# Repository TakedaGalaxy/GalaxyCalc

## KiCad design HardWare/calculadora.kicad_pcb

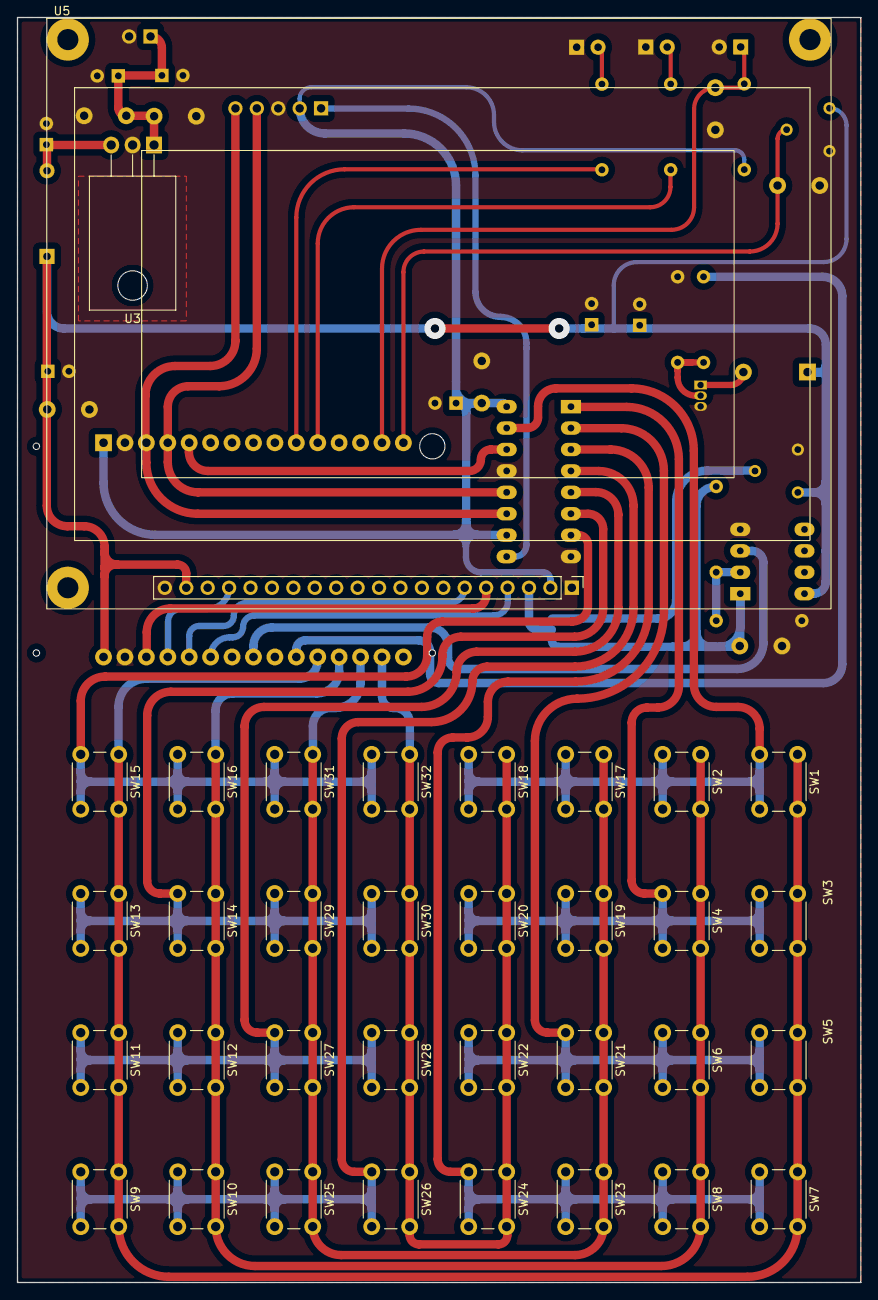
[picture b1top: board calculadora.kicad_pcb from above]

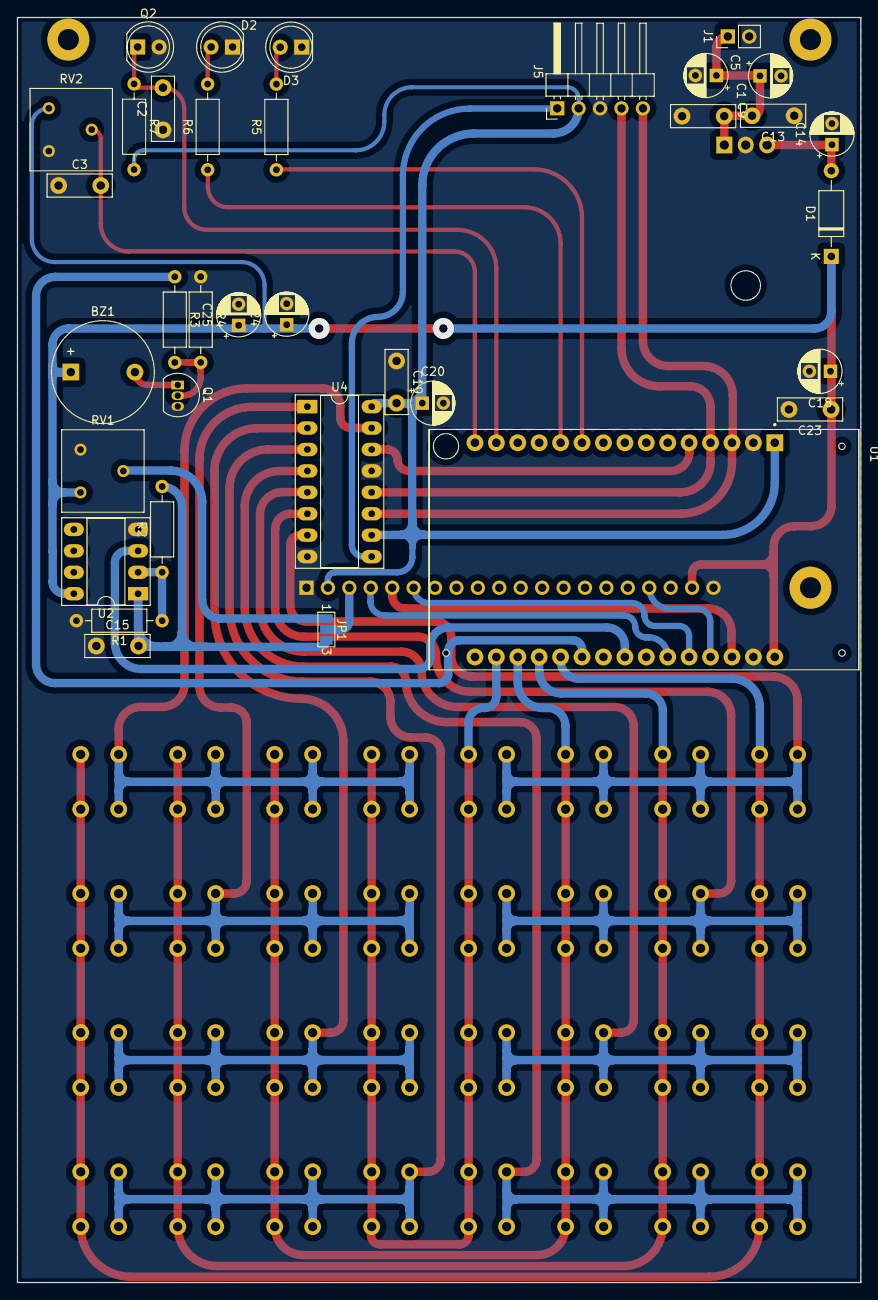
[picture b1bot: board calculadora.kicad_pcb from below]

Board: 2 copper layers, 100.0 x 150.0 mm, 69 parts (35 on the bottom side), 39 nets.

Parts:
BZ1: Buzzer; Buzzer_12x9.5RM7.6
C1, C24: 100UF/50v; CP_Radial_D5.0mm_P2.50mm
C2, C3, C9, C13, C15, C19: 0.1uf; C_Disc_D7.5mm_W2.5mm_P5.00mm
C5, C14, C18, C20, C25: 10UF/35V; CP_Radial_D5.0mm_P2.50mm
C23: 0.1uF; C_Disc_D7.5mm_W2.5mm_P5.00mm
D1: D_Schottky; D_A-405_P10.16mm_Horizontal
D2: LED_RED; LED_D5.0mm
D3: LED_IR; LED_D5.0mm
J1: Screw_Terminal_01x02; PinHeader_1x02_P2.54mm_Vertical
J5: Conector ShiftRegister; PinHeader_1x05_P2.54mm_Horizontal
JP1: Jumper_3_Open; SolderJumper-3_P1.3mm_Open_Pad1.0x1.5mm_NumberLabels
Q1: Q_NPN_CBE; TO-92L_Inline
Q2: Q_Photo_NPN; LED_D5.0mm
R1: 20K; R_Axial_DIN0207_L6.3mm_D2.5mm_P10.16mm_Horizontal
R2: 11K; R_Axial_DIN0207_L6.3mm_D2.5mm_P10.16mm_Horizontal
R3: 1K; R_Axial_DIN0207_L6.3mm_D2.5mm_P10.16mm_Horizontal
R4: 10K; R_Axial_DIN0207_L6.3mm_D2.5mm_P10.16mm_Horizontal
R5, R6: 100; R_Axial_DIN0207_L6.3mm_D2.5mm_P10.16mm_Horizontal
R7: 100K; R_Axial_DIN0207_L6.3mm_D2.5mm_P10.16mm_Horizontal
RV1, RV2: 10K; Potentiometer_Bourns_3386F_Vertical
SW1, SW2, SW3, SW4, SW5, SW6, SW7, SW8, SW9, SW10, SW11, SW12, SW13, SW14, SW15, SW16, SW17, SW18, SW19, SW20, SW21, SW22, SW23, SW24, SW25, SW26, SW27, SW28, SW29, SW30, SW31, SW32: chave_tactil; SW_PUSH_6mm_H5mm
U1: ESP32-DEVKIT-V1; MODULE_ESP32_DEVKIT_V1
U2: LM358; DIP-8_W7.62mm_Socket_LongPads
U3: LM7805_TO220; TO-220-3_Horizontal_TabDown
U4: M74HC595B1; DIP-16_W7.62mm_Socket_LongPads
U5: LCD_GRAFICO_ST920; Display 128x64

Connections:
+3V3: C19.2, C20.1, J5.2, R7.2, U1.1 (3V3), U4.10 (!SCLR), U4.16 (VCC), U5.2 (Vdd)
+5V: BZ1.1 (-), C18.1, C23.1, C24.1, C25.1, D1.1 (K), RV1.1, RV2.3, U1.30 (VIN), U2.8 (V+), U5.19 (A(+))
Buzzer: R3.1, U1.21 (D32)
C1: SW1.2, SW2.2, SW17.2, SW18.2, U4.15 (QA)
C2: SW3.2, SW4.2, SW19.2, SW20.2, U4.1 (QB)
C3: SW5.2, SW6.2, SW21.2, SW22.2, U4.2 (QC)
C4: SW7.2, SW8.2, SW23.2, SW24.2, U4.3 (QD)
C5: SW9.2, SW10.2, SW25.2, SW26.2, U4.4 (QE)
C6: SW11.2, SW12.2, SW27.2, SW28.2, U4.5 (QF)
C7: SW13.2, SW14.2, SW29.2, SW30.2, U4.6 (QG)
C8: SW15.2, SW16.2, SW31.2, SW32.2, U4.7 (QH)
CLOCK_SHIFT: J5.5, U1.3 (D15), U4.11 (SCK)
DAC1: U1.23 (D25), U2.3 (+)
DADO_SHIFT: U1.5 (D4), U4.14 (SI)
Enable: U1.26 (D14), U5.6 (E)
GND: C1.2, C2.1, C3.1, C5.2, C9.1, C13.1, C14.2, C15.1, C18.2, C19.1, C20.2, C23.2, C24.2, C25.2, D2.1 (K), D3.1 (K), J1.2, J5.3, Q1.3 (E), Q2.2 (E), R1.2, R4.1, RV1.3, RV2.1, U1.2 (GND), U1.29 (GND), U2.4 (V-), U3.2 (GND), U4.8 (GND), U4.13 (!G), U5.1 (Vss), U5.20 (K(-))
L1: SW1.1, SW3.1, SW5.1, SW7.1, SW9.1, SW11.1, SW13.1, SW15.1, U1.20 (D35)
L2: SW2.1, SW4.1, SW6.1, SW8.1, SW10.1, SW12.1, SW14.1, SW16.1, U1.19 (D34)
L3: SW17.1, SW19.1, SW21.1, SW23.1, SW25.1, SW27.1, SW29.1, SW31.1, U1.18 (VN)
L4: SW18.1, SW20.1, SW22.1, SW24.1, SW26.1, SW28.1, SW30.1, SW32.1, U1.17 (VP)
Led_Ir: R5.1, U1.10 (D19)
Led_Red: R6.1, U1.11 (D21)
unnamed: BZ1.2 (+), Q1.1 (C)
unnamed: C14.1, D1.2 (A), U3.3 (VO)
unnamed: D2.2 (A), R6.2
unnamed: D3.2 (A), R5.2
unnamed: JP1.1 (A), RV1.2
unnamed: JP1.2 (C), U5.3 (Vo)
unnamed: Q1.2 (B), R3.2, R4.2
unnamed: R1.1, R2.1, U2.2 (-)
QH: J5.1, U4.9 (QH')
RS: U1.25 (D27), U5.4 (D/I)
RW: U1.28 (D13), U5.5 (R/W)
Reset: U1.27 (D12), U5.17 (RST)
SET_SHIFT: J5.4, U1.4 (D2), U4.12 (RCK)
Sensor_Ir: C2.2, Q2.1 (C), R7.1, U1.14 (D22)
Sinal Contraste: C15.2, JP1.3 (B), R2.2, U2.1
Sinal_Analogico: C3.2, RV2.2, U1.15 (D23)
VCC: C1.1, C5.1, C9.2, C13.2, J1.1, U3.1 (VI)

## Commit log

2022-09-27 Commit inicial
2022-09-27 Desenvolvido primeiro prototipo
2022-09-28 Ajustes
